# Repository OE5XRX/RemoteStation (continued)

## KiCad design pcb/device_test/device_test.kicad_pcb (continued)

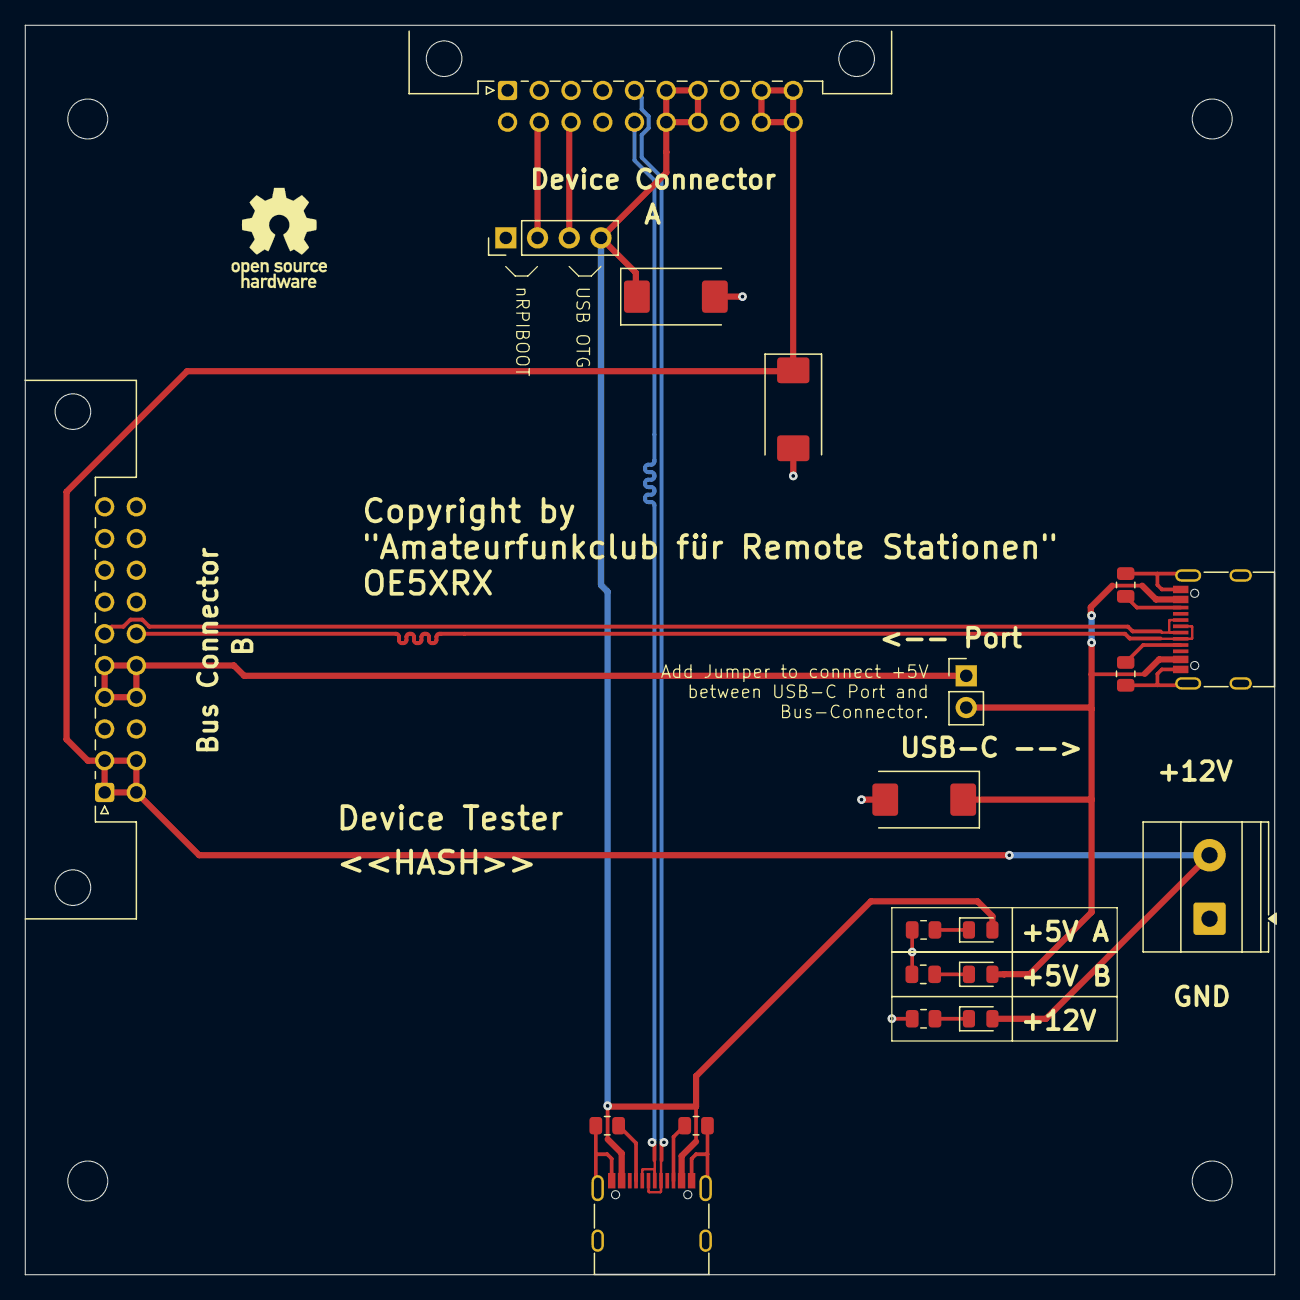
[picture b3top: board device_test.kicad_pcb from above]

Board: 4 copper layers, 100.0 x 100.0 mm, 24 parts (0 on the bottom side), 18 nets.

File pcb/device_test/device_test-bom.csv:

Row,Description,Part,References,Value,Footprint,Quantity Per PCB,Status,Datasheet,LCSC,MOUSER,Sim.Pins
1,Polarized capacitor,C_Polarized,C101 C201 C301,100u / 25V,CP_EIA-7343-43_Kemet-X,3, ,~,C132558,,
2,Light emitting diode,LED,D101 D201 D301,LED,LED_0805_2012Metric,3, ,~,C84256,,1=K 2=A
3,"Generic connector, single row, 01x04, script generated (kicad-library-utils/schlib/autogen/connector/)",Conn_01x04,J202,Conn_01x04,PinHeader_1x04_P2.54mm_Vertical,1, ,~,C2691448,,
4,"Generic connector, double row, 02x10, row letter first pin numbering scheme (pin number consists of a letter for the row and a number for the pin index in this row. a1, ..., aN; b1, ..., bN), script generated (kicad-library-utils/schlib/autogen/connector/)",Conn_02x10_Row_Letter_First,J203,Conn_02x10_Row_Letter_First,PCN10-20P-2.54DS,1, ,~,,798-PCN1020P254DS72,
5,"Generic connector, double row, 02x10, row letter first pin numbering scheme (pin number consists of a letter for the row and a number for the pin index in this row. a1, ..., aN; b1, ..., bN), script generated (kicad-library-utils/schlib/autogen/connector/)",Conn_02x10_Row_Letter_First,J302,Conn_02x10_Row_Letter_First,PCN10C-20S-2.54DS,1, ,~,,798-PCN10C20S254DS72,
6,"Generic screw terminal, single row, 01x02, script generated (kicad-library-utils/schlib/autogen/connector/)",Screw_Terminal_01x02,J101,Screw_Terminal_01x02,"TerminalBlock_Phoenix_MKDS-1,5-2-5.08_1x02_P5.08mm_Horizontal",1, ,~,C5349557,,
7,USB 2.0-only 16P Type-C Receptacle connector,USB_C_Receptacle_USB2.0_16P,J201 J301,USB_C_Receptacle_USB2.0_16P,USB_C_Receptacle_G-Switch_GT-USB-7010ASV,2, ,https://www.usb.org/sites/default/files/documents/usb_type-c.zip,C2988369,,
8,Resistor,R,R203 R303,1k,R_0805_2012Metric,2, ,~,C17513,,
9,Resistor,R,R101,2k2,R_0805_2012Metric,1, ,~,C17520,,
10,Resistor,R,R201 R202 R301 R302,5k1,R_0805_2012Metric,4, ,~,C27834,,

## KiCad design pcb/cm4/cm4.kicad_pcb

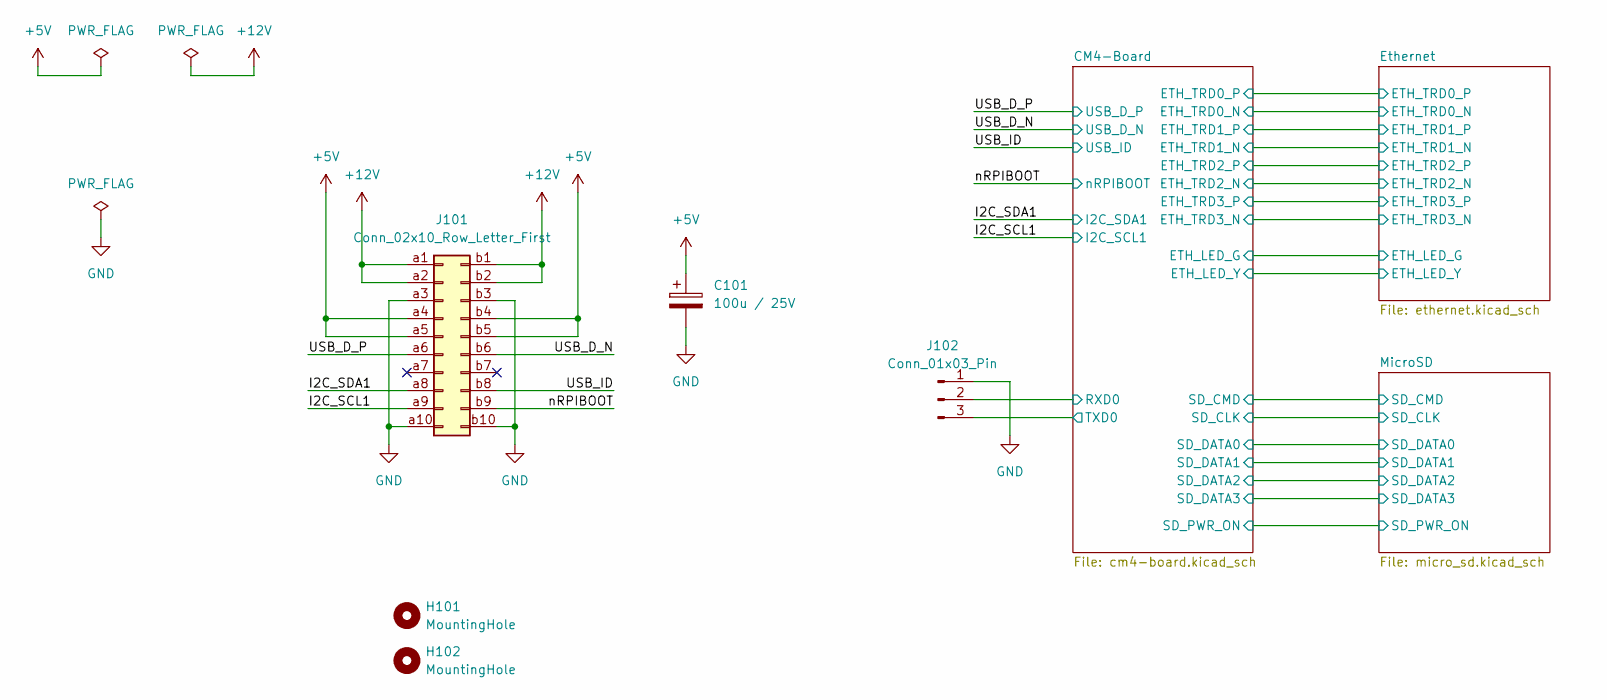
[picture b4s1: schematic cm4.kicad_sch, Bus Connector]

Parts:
C101: 100u / 25V; CP_EIA-7343-43_Kemet-X; LCSC C132558
H101, H102: MountingHole; MountingHole_3.2mm_M3
J101: Conn_02x10_Row_Letter_First; PCN10C-20S-2.54DS; MOUSER 798-PCN10C20S254DS72
J102: Conn_01x03_Pin; PinHeader_1x03_P2.54mm_Horizontal

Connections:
+5V: C101.1, J101.a4, J101.a5, J101.b4, J101.b5; also elsewhere on the board
+12V: J101.a1, J101.a2, J101.b1, J101.b2
/CM4-Board/RXD0: J102.2; also elsewhere on the board
/CM4-Board/TXD0: J102.3; also elsewhere on the board
/I2C_SCL1: J101.a9; also elsewhere on the board
/I2C_SDA1: J101.a8; also elsewhere on the board
/USB_D_N: J101.b6; also elsewhere on the board
/USB_D_P: J101.a6; also elsewhere on the board
/USB_ID: J101.b8; also elsewhere on the board
/nRPIBOOT: J101.b9; also elsewhere on the board
GND: C101.2, J101.a3, J101.a10, J101.b3, J101.b10, J102.1; also elsewhere on the board

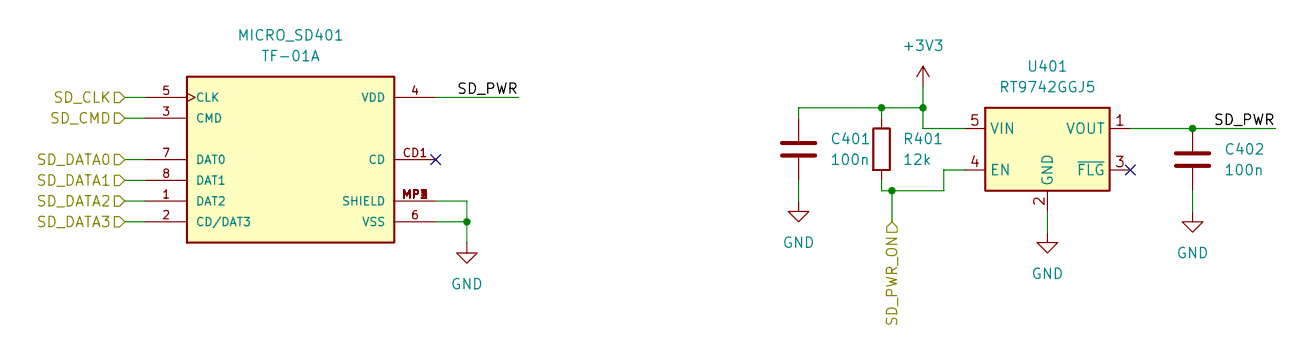
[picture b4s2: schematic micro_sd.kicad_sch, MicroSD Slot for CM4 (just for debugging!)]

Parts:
C401, C402: 100n; C_0805_2012Metric; LCSC C28233
MICRO_SD401: TF-01A; LCSC C91145
R401: 12k; R_0805_2012Metric; LCSC C17444
U401: RT9742GGJ5; TSOT-23-5; LCSC C250547

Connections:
+3V3: C401.1, R401.1, U401.5 (VIN); also elsewhere on the board
/CM4-Board/SD_CLK: MICRO_SD401.5 (CLK); also elsewhere on the board
/CM4-Board/SD_CMD: MICRO_SD401.3 (CMD); also elsewhere on the board
/CM4-Board/SD_DATA0: MICRO_SD401.7 (DAT0); also elsewhere on the board
/CM4-Board/SD_DATA1: MICRO_SD401.8 (DAT1); also elsewhere on the board
/CM4-Board/SD_DATA2: MICRO_SD401.1 (DAT2); also elsewhere on the board
/CM4-Board/SD_DATA3: MICRO_SD401.2 (CD/DAT3); also elsewhere on the board
/CM4-Board/SD_PWR_ON: R401.2, U401.4 (EN); also elsewhere on the board
/MicroSD/SD_PWR: C402.1, MICRO_SD401.4 (VDD), U401.1 (VOUT)
GND: C401.2, C402.2, MICRO_SD401.6 (VSS), MICRO_SD401.MP1 (SHIELD), MICRO_SD401.MP2 (SHIELD), MICRO_SD401.MP3 (SHIELD), MICRO_SD401.MP4 (SHIELD), U401.2 (GND); also elsewhere on the board

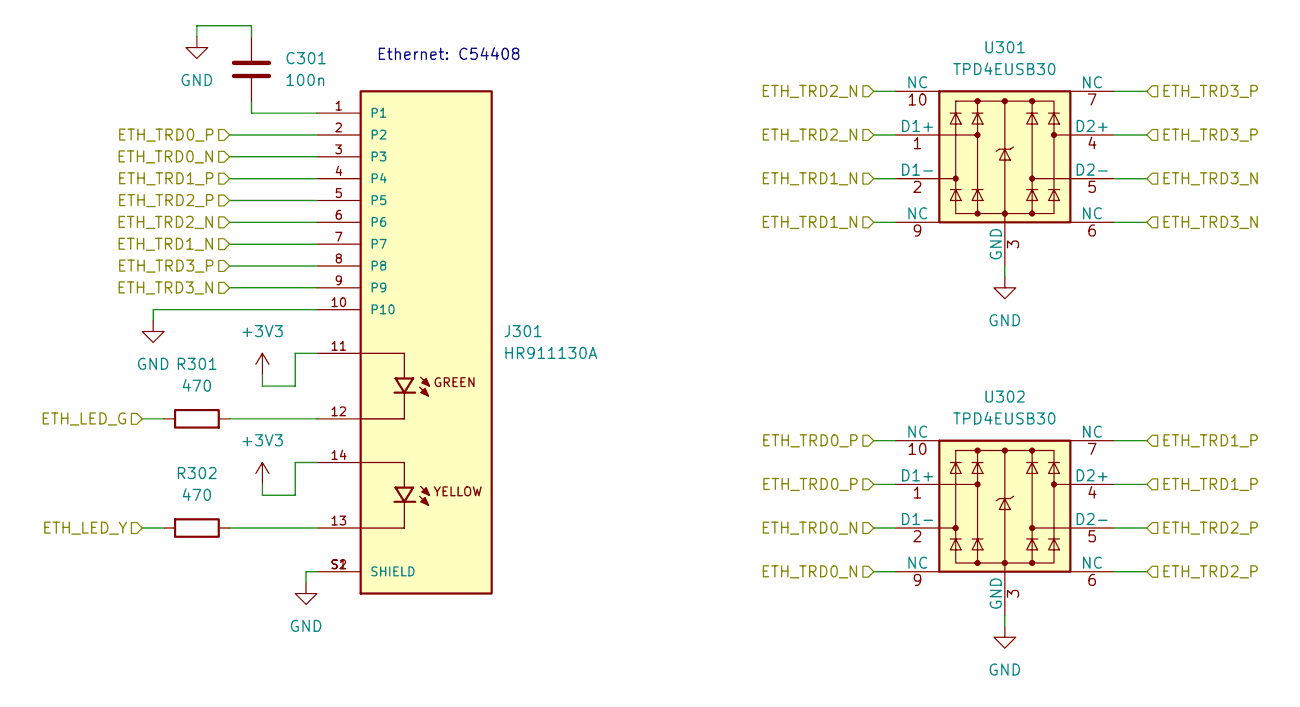
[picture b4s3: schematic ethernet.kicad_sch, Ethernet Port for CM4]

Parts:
C301: 100n; C_0805_2012Metric; LCSC C28233
J301: HR911130A; HANRUN_HR911130A; PARTREV A; LCSC C54408
R301, R302: 470; R_0805_2012Metric; LCSC C17710
U301, U302: TPD4EUSB30; USON-10_2.5x1.0mm_P0.5mm; LCSC C90627

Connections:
+3V3: J301.11, J301.14; also elsewhere on the board
/CM4-Board/ETH_LED_G: R301.1; also elsewhere on the board
/CM4-Board/ETH_LED_Y: R302.2; also elsewhere on the board
/CM4-Board/ETH_TRD0_N: J301.3, U302.2 (D1-), U302.9 (NC); also elsewhere on the board
/CM4-Board/ETH_TRD0_P: J301.2, U302.1 (D1+), U302.10 (NC); also elsewhere on the board
/CM4-Board/ETH_TRD1_N: J301.7, U301.2 (D1-), U301.9 (NC); also elsewhere on the board
/CM4-Board/ETH_TRD1_P: J301.4, U302.4 (D2+), U302.7 (NC); also elsewhere on the board
/CM4-Board/ETH_TRD2_N: J301.6, U301.1 (D1+), U301.10 (NC); also elsewhere on the board
/CM4-Board/ETH_TRD2_P: J301.5, U302.5 (D2-), U302.6 (NC); also elsewhere on the board
/CM4-Board/ETH_TRD3_N: J301.9, U301.5 (D2-), U301.6 (NC); also elsewhere on the board
/CM4-Board/ETH_TRD3_P: J301.8, U301.4 (D2+), U301.7 (NC); also elsewhere on the board
GND: C301.1, J301.10, J301.S1 (SHIELD), J301.S2 (SHIELD), U301.3 (GND), U301.8 (GND), U302.3 (GND), U302.8 (GND); also elsewhere on the board
unnamed: C301.2, J301.1
unnamed: J301.12, R301.2
unnamed: J301.13, R302.1

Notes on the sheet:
Ethernet: C54408

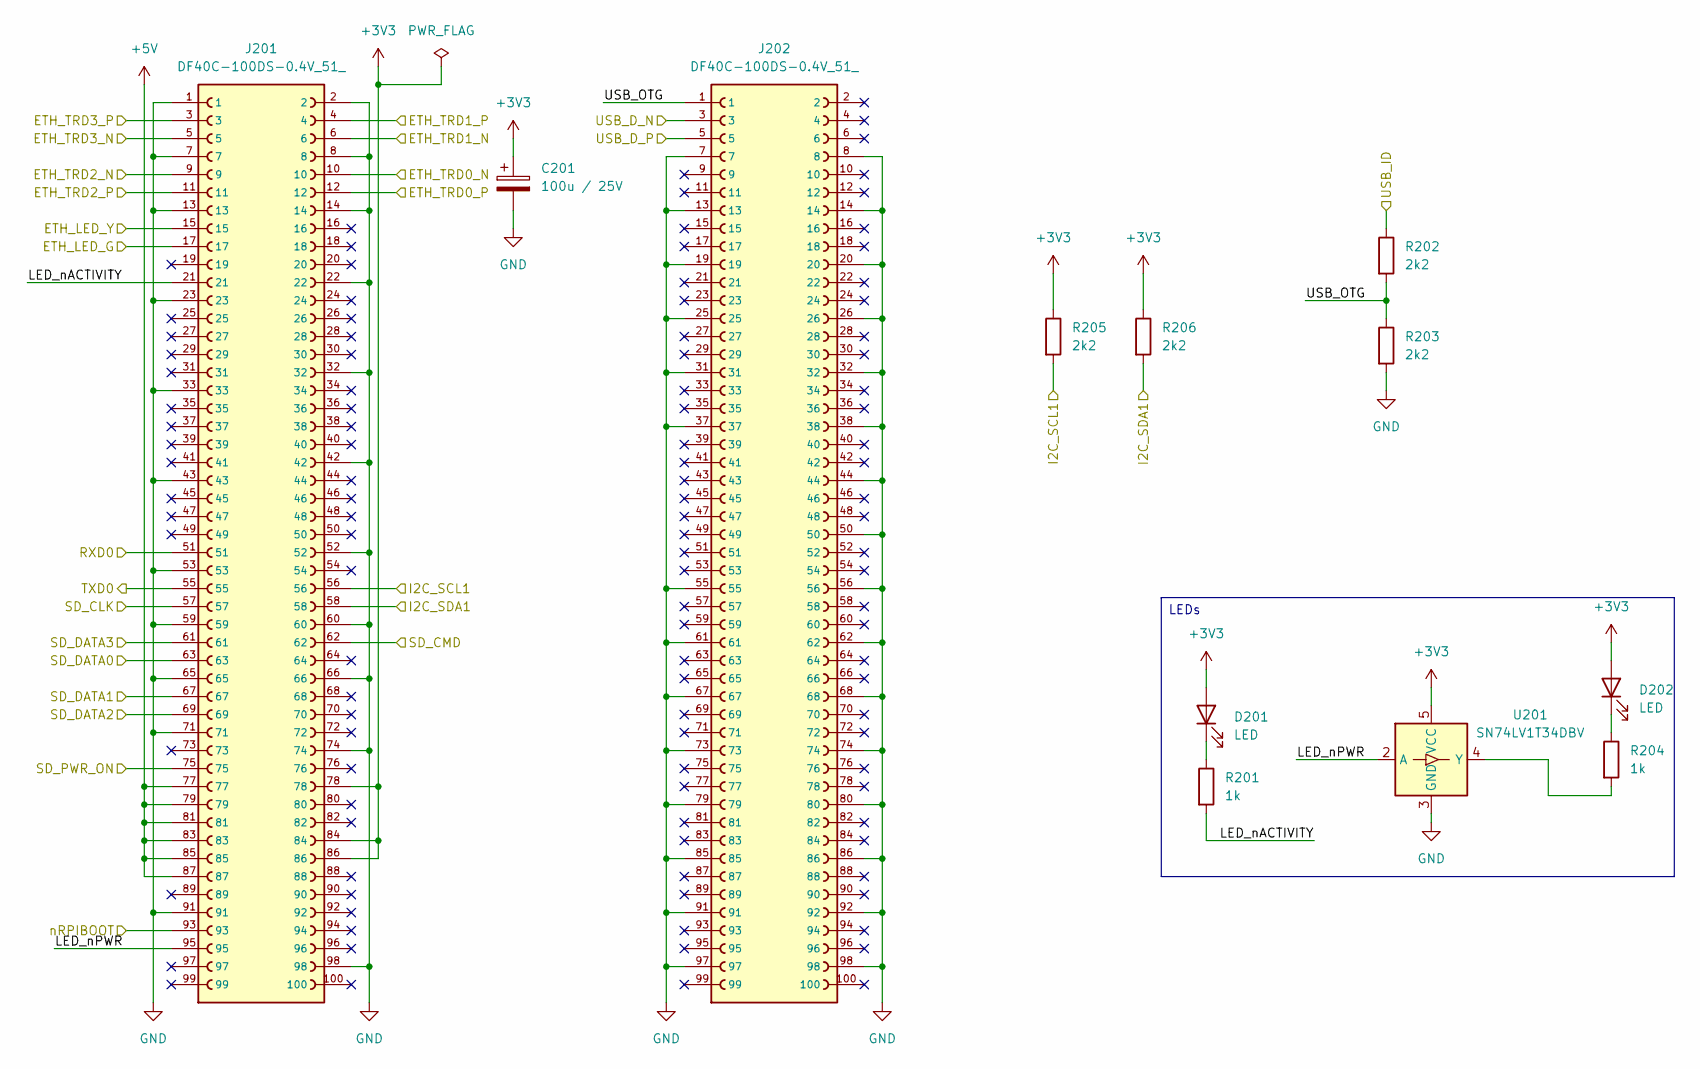
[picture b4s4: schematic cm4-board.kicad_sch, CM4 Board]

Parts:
C201: 100u / 25V; CP_EIA-7343-43_Kemet-X; LCSC C132558
D201, D202: LED; LED_0805_2012Metric; LCSC C84256
J201, J202: DF40C-100DS-0.4V_51_; HIROSE_DF40C-100DS-0.4V_51_; PARTREV Oct.1.2023; LCSC C597931
R201, R204: 1k; R_0805_2012Metric; LCSC C17513
R202, R203, R205, R206: 2k2; R_0805_2012Metric; LCSC C17520
U201: SN74LV1T34DBV; SOT-23-5; LCSC C100024

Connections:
+3V3: C201.1, D201.2 (A), D202.2 (A), J201.78, J201.84, J201.86, R205.1, R206.1, U201.5 (VCC); also elsewhere on the board
+5V: J201.77, J201.79, J201.81, J201.83, J201.85, J201.87; also elsewhere on the board
/CM4-Board/ETH_LED_G: J201.17; also elsewhere on the board
/CM4-Board/ETH_LED_Y: J201.15; also elsewhere on the board
/CM4-Board/ETH_TRD0_N: J201.10; also elsewhere on the board
/CM4-Board/ETH_TRD0_P: J201.12; also elsewhere on the board
/CM4-Board/ETH_TRD1_N: J201.6; also elsewhere on the board
/CM4-Board/ETH_TRD1_P: J201.4; also elsewhere on the board
/CM4-Board/ETH_TRD2_N: J201.9; also elsewhere on the board
/CM4-Board/ETH_TRD2_P: J201.11; also elsewhere on the board
/CM4-Board/ETH_TRD3_N: J201.5; also elsewhere on the board
/CM4-Board/ETH_TRD3_P: J201.3; also elsewhere on the board
/CM4-Board/LED_nACTIVITY: J201.21, R201.2
/CM4-Board/LED_nPWR: J201.95, U201.2 (A)
/CM4-Board/RXD0: J201.51; also elsewhere on the board
/CM4-Board/SD_CLK: J201.57; also elsewhere on the board
/CM4-Board/SD_CMD: J201.62; also elsewhere on the board
/CM4-Board/SD_DATA0: J201.63; also elsewhere on the board
/CM4-Board/SD_DATA1: J201.67; also elsewhere on the board
/CM4-Board/SD_DATA2: J201.69; also elsewhere on the board
/CM4-Board/SD_DATA3: J201.61; also elsewhere on the board
/CM4-Board/SD_PWR_ON: J201.75; also elsewhere on the board
/CM4-Board/TXD0: J201.55; also elsewhere on the board
/CM4-Board/USB_OTG: J202.1, R202.2, R203.1
/I2C_SCL1: J201.56, R205.2; also elsewhere on the board
/I2C_SDA1: J201.58, R206.2; also elsewhere on the board
/USB_D_N: J202.3; also elsewhere on the board
/USB_D_P: J202.5; also elsewhere on the board
/USB_ID: R202.1; also elsewhere on the board
/nRPIBOOT: J201.93; also elsewhere on the board
GND: C201.2, J201.1, J201.2, J201.7, J201.8, J201.13, J201.14, J201.22, J201.23, J201.32, J201.33, J201.42, J201.43, J201.52, J201.53, J201.59, J201.60, J201.65, J201.66, J201.71, J201.74, J201.91, J201.98, J202.7, J202.8, J202.13, J202.14, J202.19, J202.20, J202.25, J202.26, J202.31, J202.32, J202.37, J202.38, J202.44, J202.50, J202.55, J202.56, J202.61, J202.62, J202.67, J202.68, J202.73, J202.74, J202.79, J202.80, J202.85, J202.86, J202.91, J202.92, J202.97, J202.98, R203.2, U201.3 (GND); also elsewhere on the board
unnamed: D201.1 (K), R201.1
unnamed: D202.1 (K), R204.1
unnamed: R204.2, U201.4 (Y)

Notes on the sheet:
LEDs

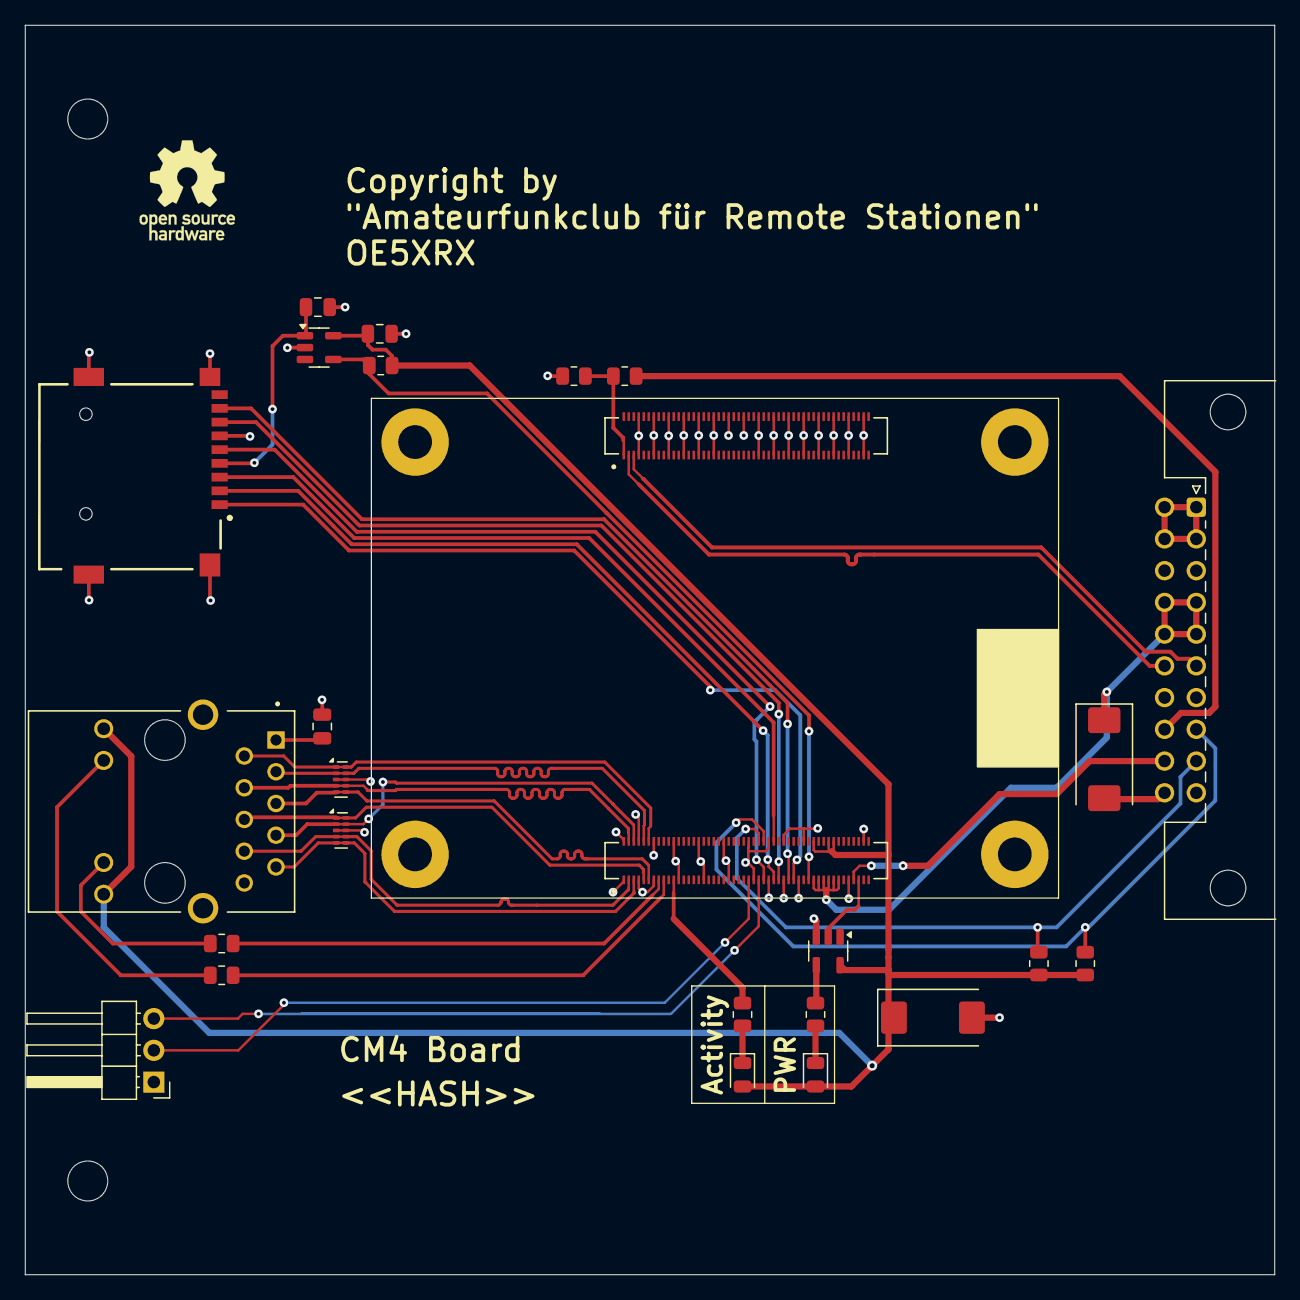
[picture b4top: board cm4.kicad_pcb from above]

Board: 4 copper layers, 100.0 x 100.0 mm, 28 parts (0 on the bottom side), 39 nets.

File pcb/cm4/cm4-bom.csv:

Row,Description,Part,References,Value,Footprint,Quantity Per PCB,Status,Datasheet,LCSC,MOUSER,MF,Description_1,Package,Price,SnapEDA_Link,MP,Availability,Check_prices,MAXIMUM_PACKAGE_HEIGHT,STANDARD,PARTREV,MANUFACTURER,Sim.Pins
1,Unpolarized capacitor,C,C301 C401 C402,100n,C_0805_2012Metric,3, ,~,C28233,,,,,,,,,,,,,,
2,Polarized capacitor,C_Polarized,C101 C201,100u / 25V,CP_EIA-7343-43_Kemet-X,2, ,~,C132558,,,,,,,,,,,,,,
3,Light emitting diode,LED,D201 D202,LED,LED_0805_2012Metric,2, ,~,C84256,,,,,,,,,,,,,,1=K 2=A
4,"Generic connector, double row, 02x10, row letter first pin numbering scheme (pin number consists of a letter for the row and a number for the pin index in this row. a1, ..., aN; b1, ..., bN), script generated (kicad-library-utils/schlib/autogen/connector/)",Conn_02x10_Row_Letter_First,J101,Conn_02x10_Row_Letter_First,PCN10C-20S-2.54DS,1, ,~,,798-PCN10C20S254DS72,,,,,,,,,,,,,
5,"100 Position Connector Receptacle, Center Strip Contacts Surface Mount Gold",DF40C-100DS-0.4V_51_,J201 J202,DF40C-100DS-0.4V_51_,HIROSE_DF40C-100DS-0.4V_51_,2, ,,C597931,,Hirose,"100 Position Connector Receptacle, Center Strip Contacts Surface Mount Gold",None,None,https://www.snapeda.com/parts/DF40C-100DS-0.4V(51)/Hirose/vi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,DF40C-100DS-0.4V(51),In Stock,https://www.snapeda.com/parts/DF40C-100DS-0.4V(51)/Hirose/vi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,1.65mm,Manufacturer Recommendations,Oct.1.2023,Hirose,
6,RJ45 Connector,HR911130A,J301,HR911130A,HANRUN_HR911130A,1, ,,C54408,,hanrun,,None,None,https://www.snapeda.com/parts/HR911130A/HanRun/view-part/?ref=snap,HR911130A,In Stock,https://www.snapeda.com/parts/HR911130A/HanRun/view-part/?ref=eda,13.75 mm,Manufacturer Recommendations,A,HanRun,
7,MicroSD Card Slot,TF-01A,MICRO_SD401,TF-01A,TF-01A,1, ,,C91145,,"HRO Electronics Co., Ltd.",Standard Card Edge Connectors,Package,None,https://www.snapeda.com/parts/TF-01A/HRO+Electronics+Co.%252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,TF-01A,Not in stock,https://www.snapeda.com/parts/TF-01A/HRO+Electronics+Co.%252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,,,,,
8,Resistor,R,R301 R302,470,R_0805_2012Metric,2, ,~,C17710,,,,,,,,,,,,,,
9,Resistor,R,R201 R204,1k,R_0805_2012Metric,2, ,~,C17513,,,,,,,,,,,,,,
10,Resistor,R,R202 R203 R205 R206,2k2,R_0805_2012Metric,4, ,~,C17520,,,,,,,,,,,,,,
11,Resistor,R,R401,12k,R_0805_2012Metric,1, ,~,C17444,,,,,,,,,,,,,,
12,,RT9742AGJ5F,U401,RT9742GGJ5,TSOT-23-5,1, ,,C250547,,,,,,,,,,,,,,
13,"Single Power Supply, Single Buffer GATE, CMOS Logic, Level Shifter, SOT-23-5",SN74LV1T34DBV,U201,SN74LV1T34DBV,SOT-23-5,1, ,https://www.ti.com/lit/ds/symlink/sn74lv1t34.pdf,C100024,,,,,,,,,,,,,,
14,"4-Channel ESD Protection for Super-Speed USB 3.0 Interface, USON-10",TPD4EUSB30,U301 U302,TPD4EUSB30,USON-10_2.5x1.0mm_P0.5mm,2, ,http://www.ti.com/lit/ds/symlink/tpd2eusb30a.pdf,C90627,,,,,,,,,,,,,,

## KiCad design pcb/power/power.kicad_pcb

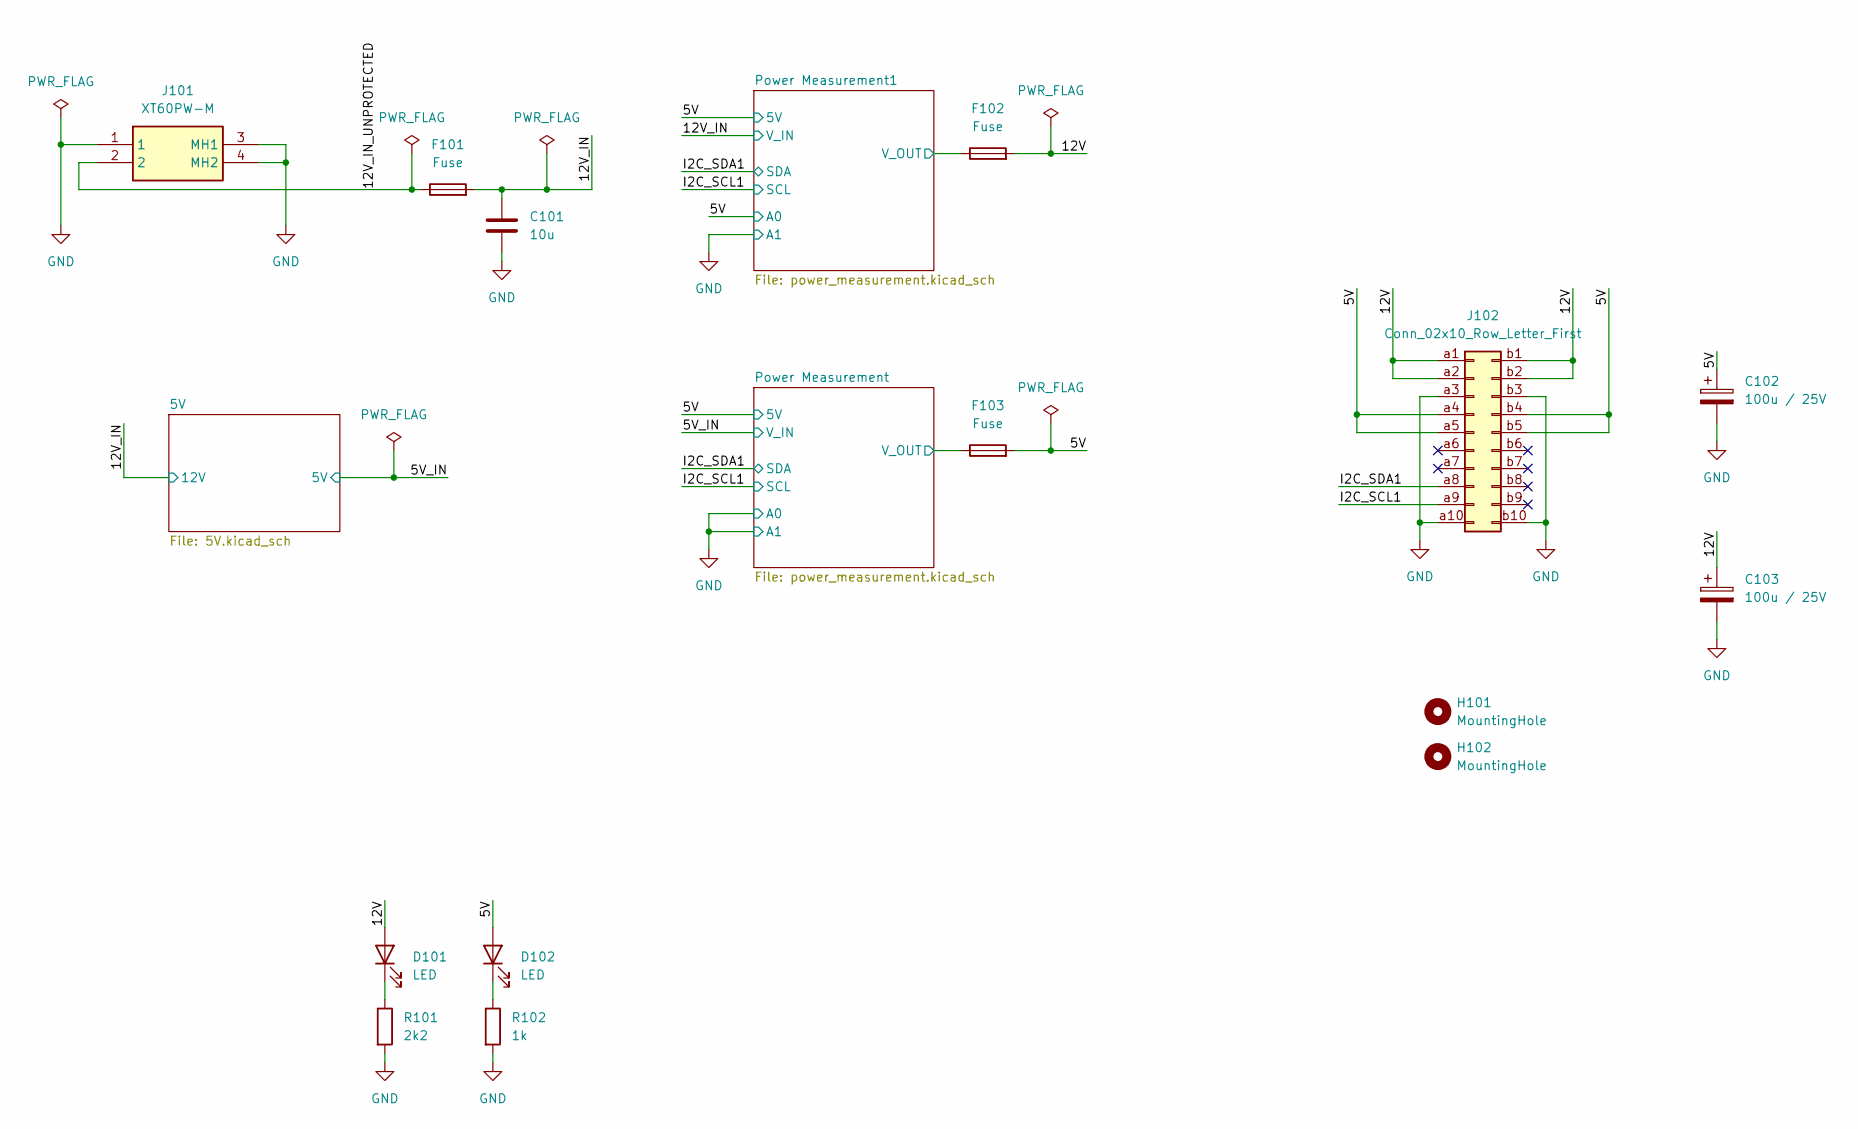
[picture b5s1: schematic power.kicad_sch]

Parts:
C101: 10u; C_1206_3216Metric; LCSC C13585
C102, C103: 100u / 25V; CP_EIA-7343-43_Kemet-X; LCSC C132558
D101, D102: LED; LED_0805_2012Metric; LCSC C84256
F101, F102, F103: Fuse; FUSE_01530007Z; MOUSER 576-01530007Z
H101, H102: MountingHole; MountingHole_3.2mm_M3
J101: XT60PW-M; XT60PWM
J102: Conn_02x10_Row_Letter_First; PCN10C-20S-2.54DS; MOUSER 798-PCN10C20S254DS72
R101: 2k2; R_0805_2012Metric; LCSC C17520
R102: 1k; R_0805_2012Metric; LCSC C17513

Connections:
/5V: C102.1, D102.2 (A), F103.2, J102.a4, J102.a5, J102.b4, J102.b5; also elsewhere on the board
/12V: C103.1, D101.2 (A), F102.2, J102.a1, J102.a2, J102.b1, J102.b2
/12V_IN: C101.1, F101.2; also elsewhere on the board
/12V_IN_UNPROTECTED: F101.1, J101.2
/I2C_SCL1: J102.a9; also elsewhere on the board
/I2C_SDA1: J102.a8; also elsewhere on the board
/Power Measurement1/V_OUT: F102.1; also elsewhere on the board
/Power Measurement/V_OUT: F103.1; also elsewhere on the board
GND: C101.2, C102.2, C103.2, J101.1, J101.3 (MH1), J101.4 (MH2), J102.a3, J102.a10, J102.b3, J102.b10, R101.2, R102.2; also elsewhere on the board
unnamed: D101.1 (K), R101.1
unnamed: D102.1 (K), R102.1

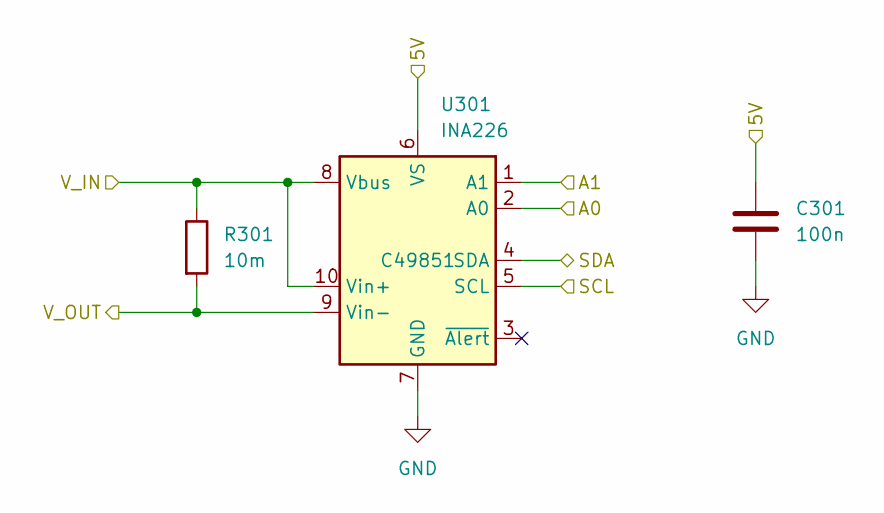
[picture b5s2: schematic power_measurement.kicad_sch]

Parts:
C301: 100n; C_0805_2012Metric; LCSC C28233
R301: 10m; R_2512_6332Metric; MOUSER 652-CRF2512FZR010ELF
U301: INA226; VSSOP-10_3x3mm_P0.5mm; LCSC C49851

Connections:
/5V: C301.1, U301.6 (VS); also elsewhere on the board
/5V_IN: R301.1, U301.8 (Vbus), U301.10 (Vin+); also elsewhere on the board
/I2C_SCL1: U301.5 (SCL); also elsewhere on the board
/I2C_SDA1: U301.4 (SDA); also elsewhere on the board
/Power Measurement/V_OUT: R301.2, U301.9 (Vin-); also elsewhere on the board
GND: C301.2, U301.1 (A1), U301.2 (A0), U301.7 (GND); also elsewhere on the board

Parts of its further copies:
C401: 100n; C_0805_2012Metric; LCSC C28233
R401: 10m; R_2512_6332Metric; MOUSER 652-CRF2512FZR010ELF
U401: INA226; VSSOP-10_3x3mm_P0.5mm; LCSC C49851

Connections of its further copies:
/5V: C401.1, U401.2 (A0), U401.6 (VS); also elsewhere on the board
/12V_IN: R401.1, U401.8 (Vbus), U401.10 (Vin+); also elsewhere on the board
/I2C_SCL1: U401.5 (SCL); also elsewhere on the board
/I2C_SDA1: U401.4 (SDA); also elsewhere on the board
/Power Measurement1/V_OUT: R401.2, U401.9 (Vin-); also elsewhere on the board
GND: C401.2, U401.1 (A1), U401.7 (GND); also elsewhere on the board

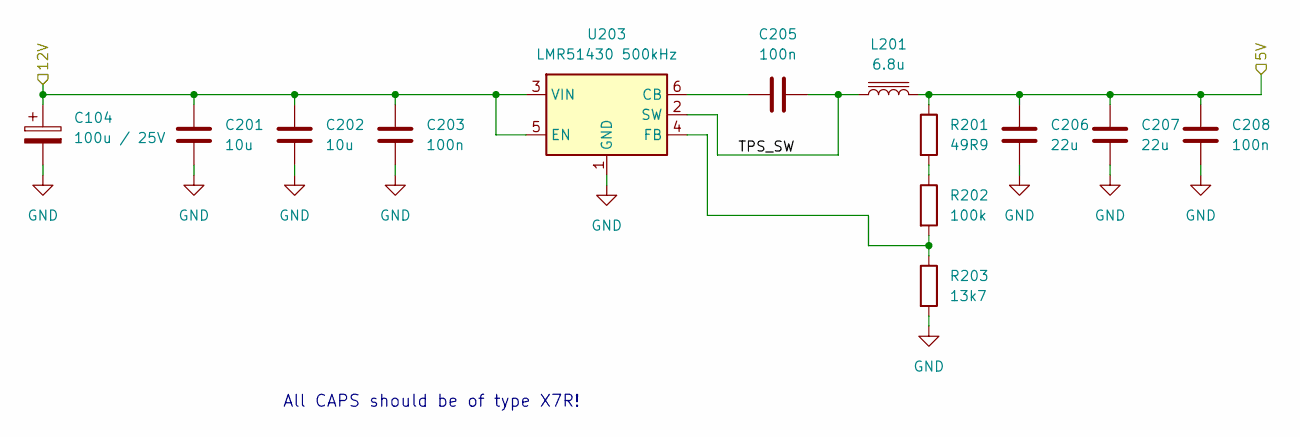
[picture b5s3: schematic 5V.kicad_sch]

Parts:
C104: 100u / 25V; CP_EIA-7343-43_Kemet-X; LCSC C132558
C201, C202: 10u; C_1206_3216Metric; LCSC C13585
C203, C205, C208: 100n; C_0805_2012Metric; LCSC C28233
C206, C207: 22u; C_1206_3216Metric; LCSC C12891
L201: 6.8u; WE-XHMI_6060; MOUSER 710-74439346068
R201: 49R9; R_0805_2012Metric; MOUSER 667-ERA-6AED49R9V
R202: 100k; R_0805_2012Metric; MOUSER 603-RC0805JR-07100KL
R203: 13k7; R_0805_2012Metric; MOUSER 652-CR0805FX-1372ELF
U203: LMR51430 500kHz; SOT-23-6; MOUSER 595-LMR51430XDDCR

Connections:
/5V/TPS_SW: C205.2, L201.1, U203.2 (SW)
/5V_IN: C206.2, C207.2, C208.2, L201.2, R201.1; also elsewhere on the board
/12V_IN: C104.1, C201.1, C202.1, C203.1, U203.3 (VIN), U203.5 (EN); also elsewhere on the board
GND: C104.2, C201.2, C202.2, C203.2, C206.1, C207.1, C208.1, R203.2, U203.1 (GND); also elsewhere on the board
unnamed: R201.2, R202.1
unnamed: C205.1, U203.6 (CB)
unnamed: R202.2, R203.1, U203.4 (FB)

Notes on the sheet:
All CAPS should be of type X7R!

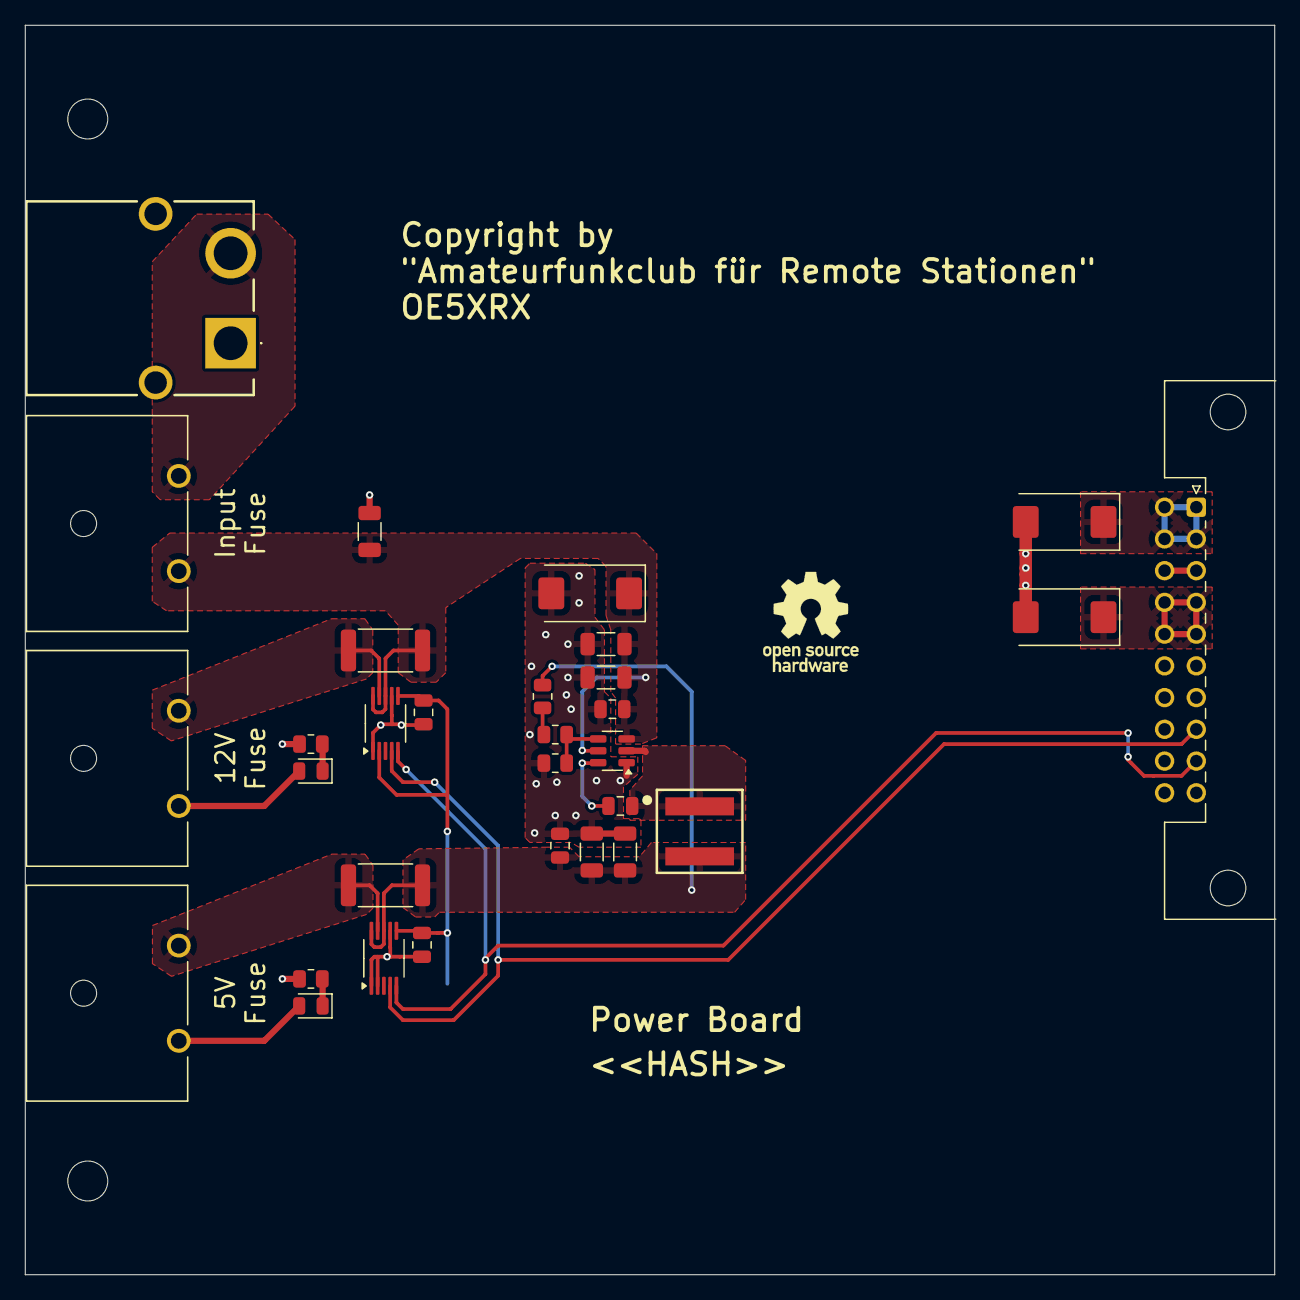
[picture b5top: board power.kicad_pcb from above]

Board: 4 copper layers, 100.0 x 100.0 mm, 33 parts (0 on the bottom side), 16 nets.

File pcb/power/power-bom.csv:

Row,Description,Part,References,Value,Footprint,Quantity Per PCB,Status,Datasheet,LCSC,MOUSER,Sim.Pins,Height,TME Electronic Components Part Number,TME Electronic Components Price/Stock,Manufacturer_Name,Manufacturer_Part_Number
1,Unpolarized capacitor,C,C203 C205 C208 C301 C401,100n,C_0805_2012Metric,5, ,~,C28233,,,,,,,
2,Unpolarized capacitor,C,C101 C201 C202,10u,C_1206_3216Metric,3, ,~,C13585,,,,,,,
3,Unpolarized capacitor,C,C206 C207,22u,C_1206_3216Metric,2, ,~,C12891,,,,,,,
4,Polarized capacitor,C_Polarized,C102 C103 C104,100u / 25V,CP_EIA-7343-43_Kemet-X,3, ,~,C132558,,,,,,,
5,Light emitting diode,LED,D101 D102,LED,LED_0805_2012Metric,2, ,~,C84256,,1=K 2=A,,,,,
6,Fuse,Fuse,F101 F102 F103,Fuse,FUSE_01530007Z,3, ,~,C19727304,,,,,,,
7,"Generic connector, double row, 02x10, row letter first pin numbering scheme (pin number consists of a letter for the row and a number for the pin index in this row. a1, ..., aN; b1, ..., bN), script generated (kicad-library-utils/schlib/autogen/connector/)",Conn_02x10_Row_Letter_First,J102,Conn_02x10_Row_Letter_First,PCN10C-20S-2.54DS,1, ,~,,798-PCN10C20S254DS72,,,,,,
8,Connector: DC supply; socket; XT60; male; PIN: 2; on PCBs; THT; 30A,XT60PW-M,J101,XT60PW-M,XT60PWM,1, ,https://www.tme.eu/Document/b13629717d44ae038681dba08d18c0b6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,,,,8.4,,,Amass,XT60PW-M
9,Inductor with iron core,L_Iron,L201,6.8u,WE-XHMI_6060,1, ,~,C167231,,,,,,,
10,Resistor,R,R301 R401,10m,R_2512_6332Metric,2, ,~,,,,,,,,
11,Resistor,R,R201,49R9,R_0805_2012Metric,1, ,~,,667-ERA-6AED49R9V,,,,,,
12,Resistor,R,R102,1k,R_0805_2012Metric,1, ,~,C17513,,,,,,,
13,Resistor,R,R101,2k2,R_0805_2012Metric,1, ,~,C17520,,,,,,,
14,Resistor,R,R203,13k7,R_0805_2012Metric,1, ,~,,,,,,,,
15,Resistor,R,R202,100k,R_0805_2012Metric,1, ,~,,,,,,,,
16,"High-Side or Low-Side Measurement, Bi-Directional Current and Power Monitor (0-36V) with I2C Compatible Interface, VSSOP-10",INA226,U301 U401,INA226,VSSOP-10_3x3mm_P0.5mm,2, ,http://www.ti.com/lit/ds/symlink/ina226.pdf,C49851,,,,,,,
17,"4.5-V to 36-V, 3-A synchronous buck converter with 40-µA IQ, SOT-23-6",LMR51430,U203,LMR51430 500kHz,SOT-23-6,1, ,https://www.ti.com/lit/ds/symlink/lmr51430.pdf,,,,,,,,
